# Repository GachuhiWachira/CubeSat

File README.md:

# CubeSat
Outer Casing Designs from Fusion 360

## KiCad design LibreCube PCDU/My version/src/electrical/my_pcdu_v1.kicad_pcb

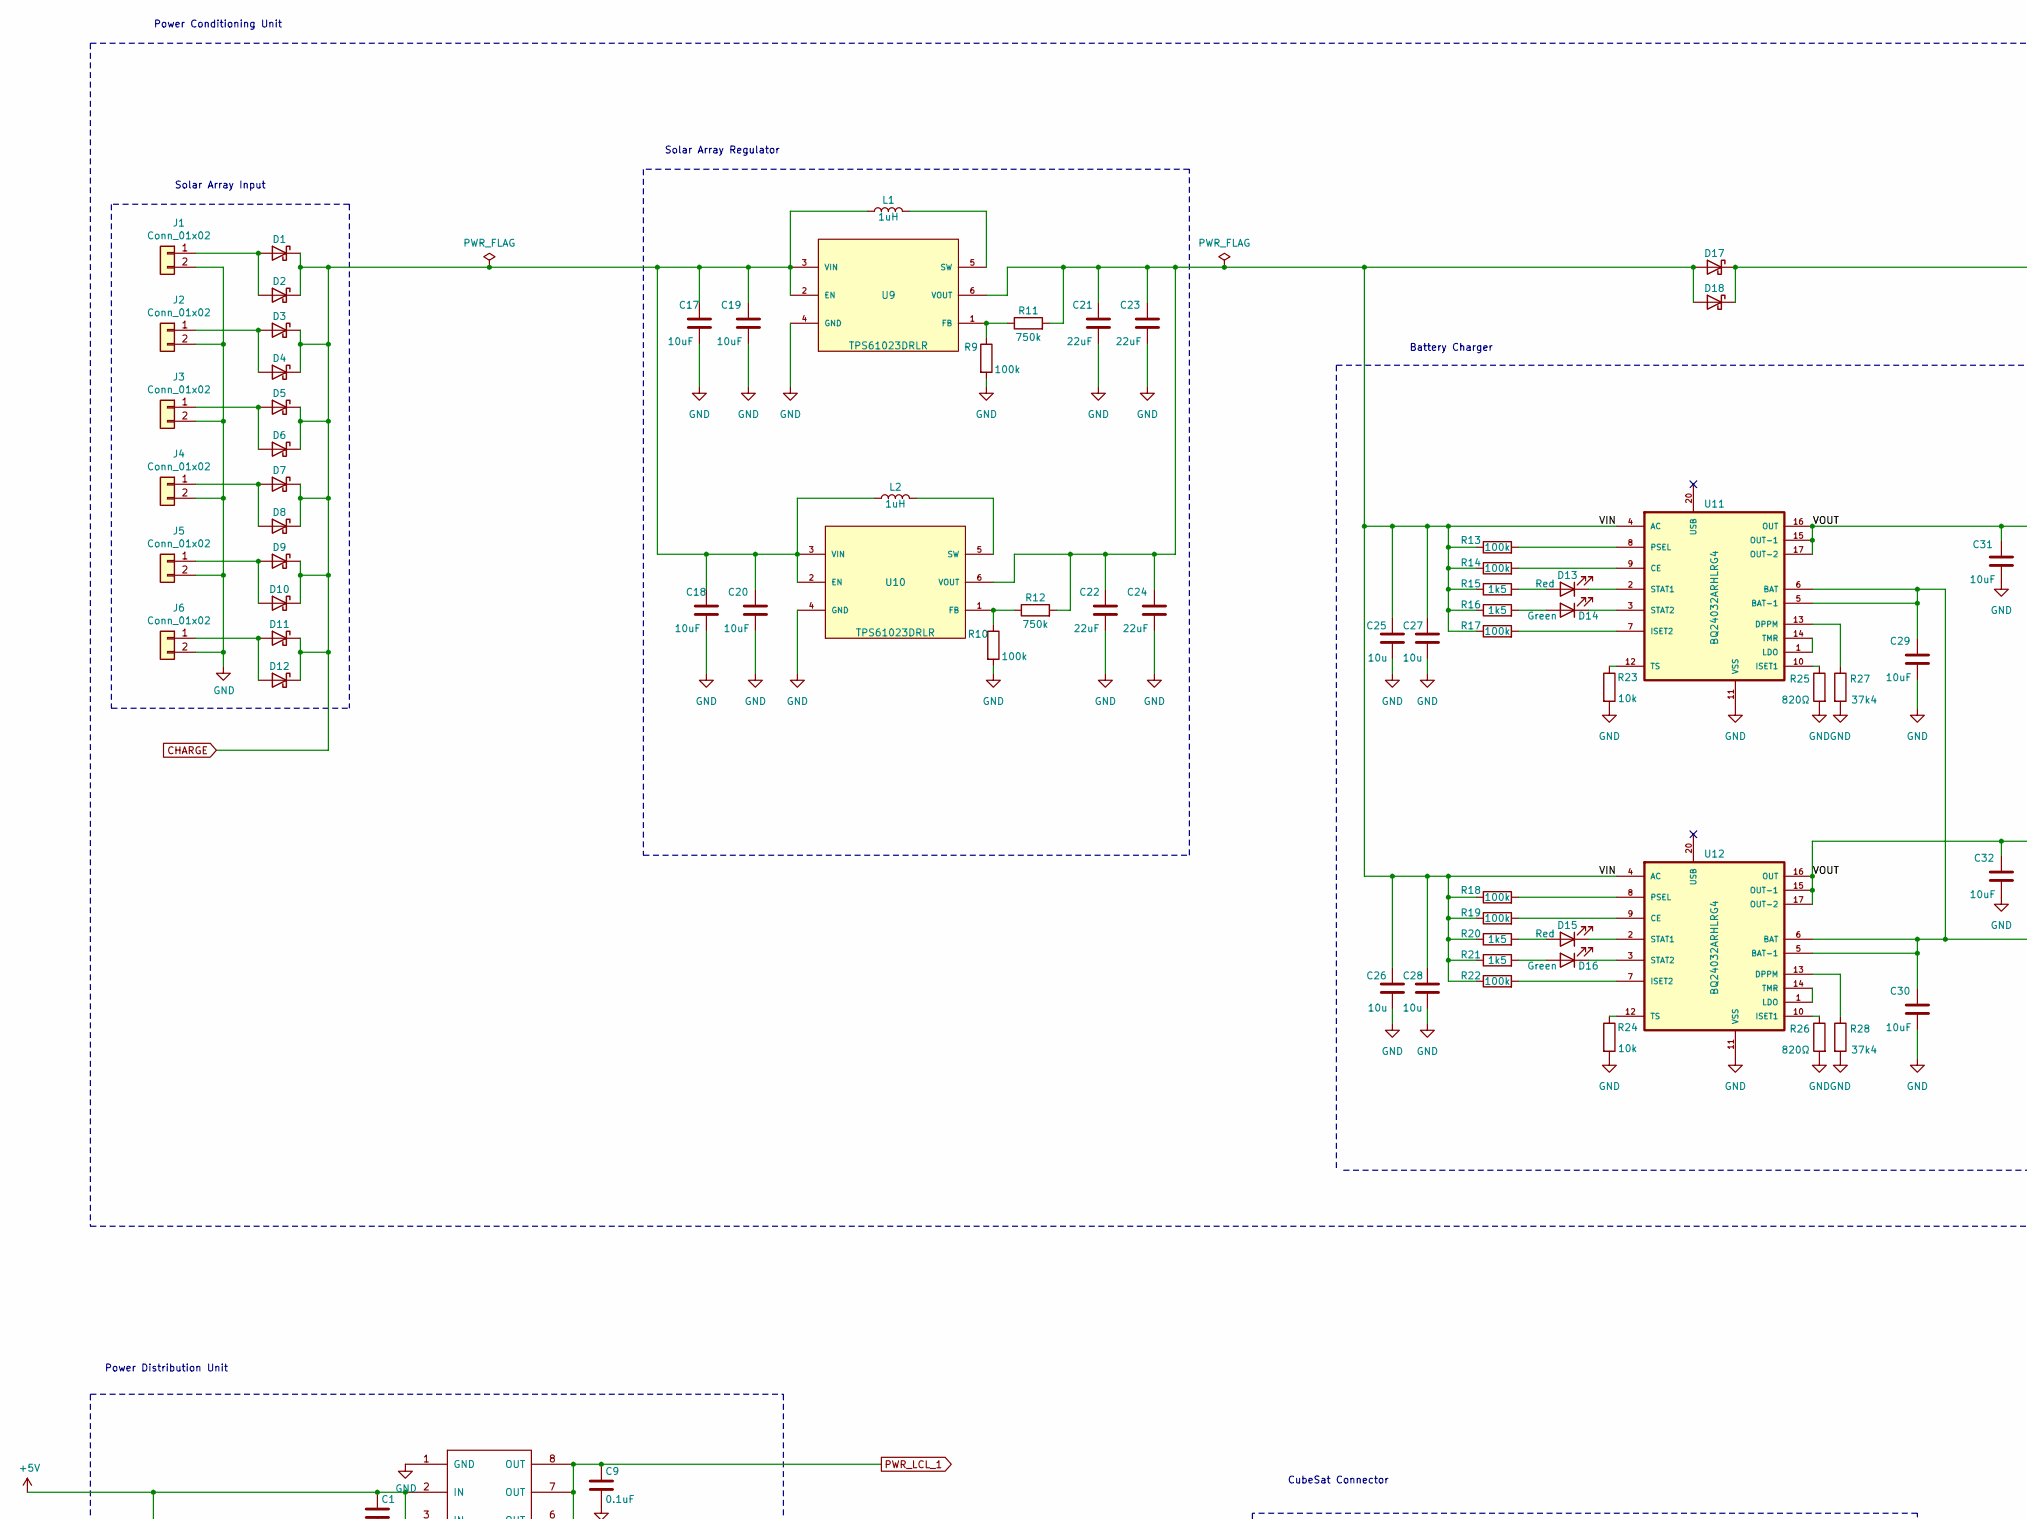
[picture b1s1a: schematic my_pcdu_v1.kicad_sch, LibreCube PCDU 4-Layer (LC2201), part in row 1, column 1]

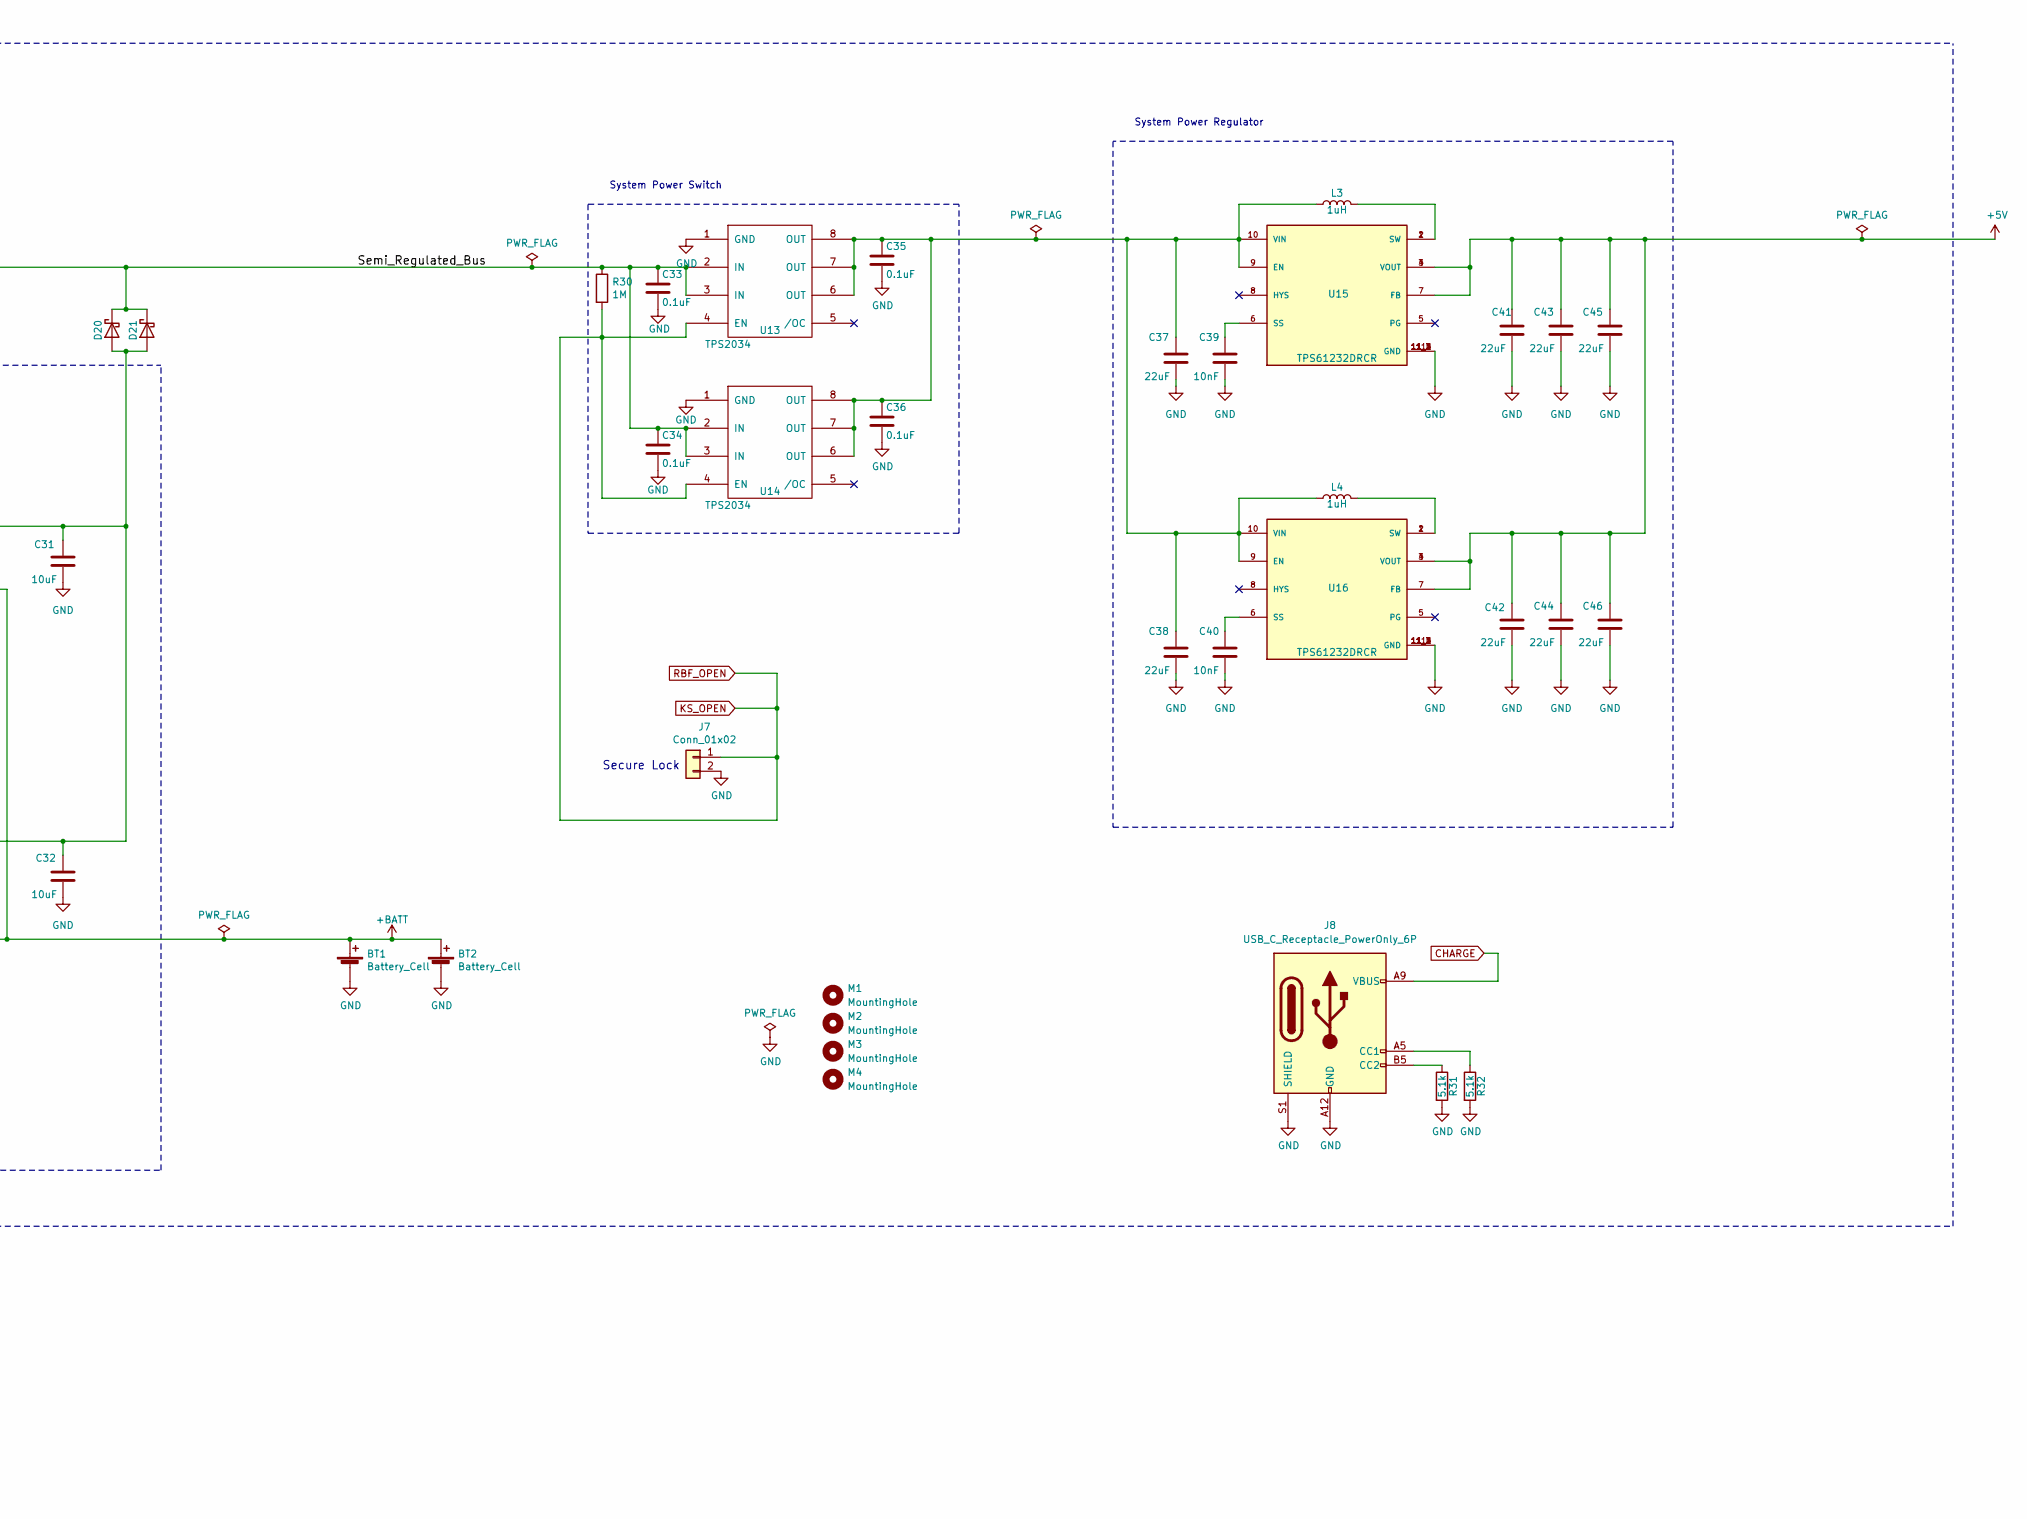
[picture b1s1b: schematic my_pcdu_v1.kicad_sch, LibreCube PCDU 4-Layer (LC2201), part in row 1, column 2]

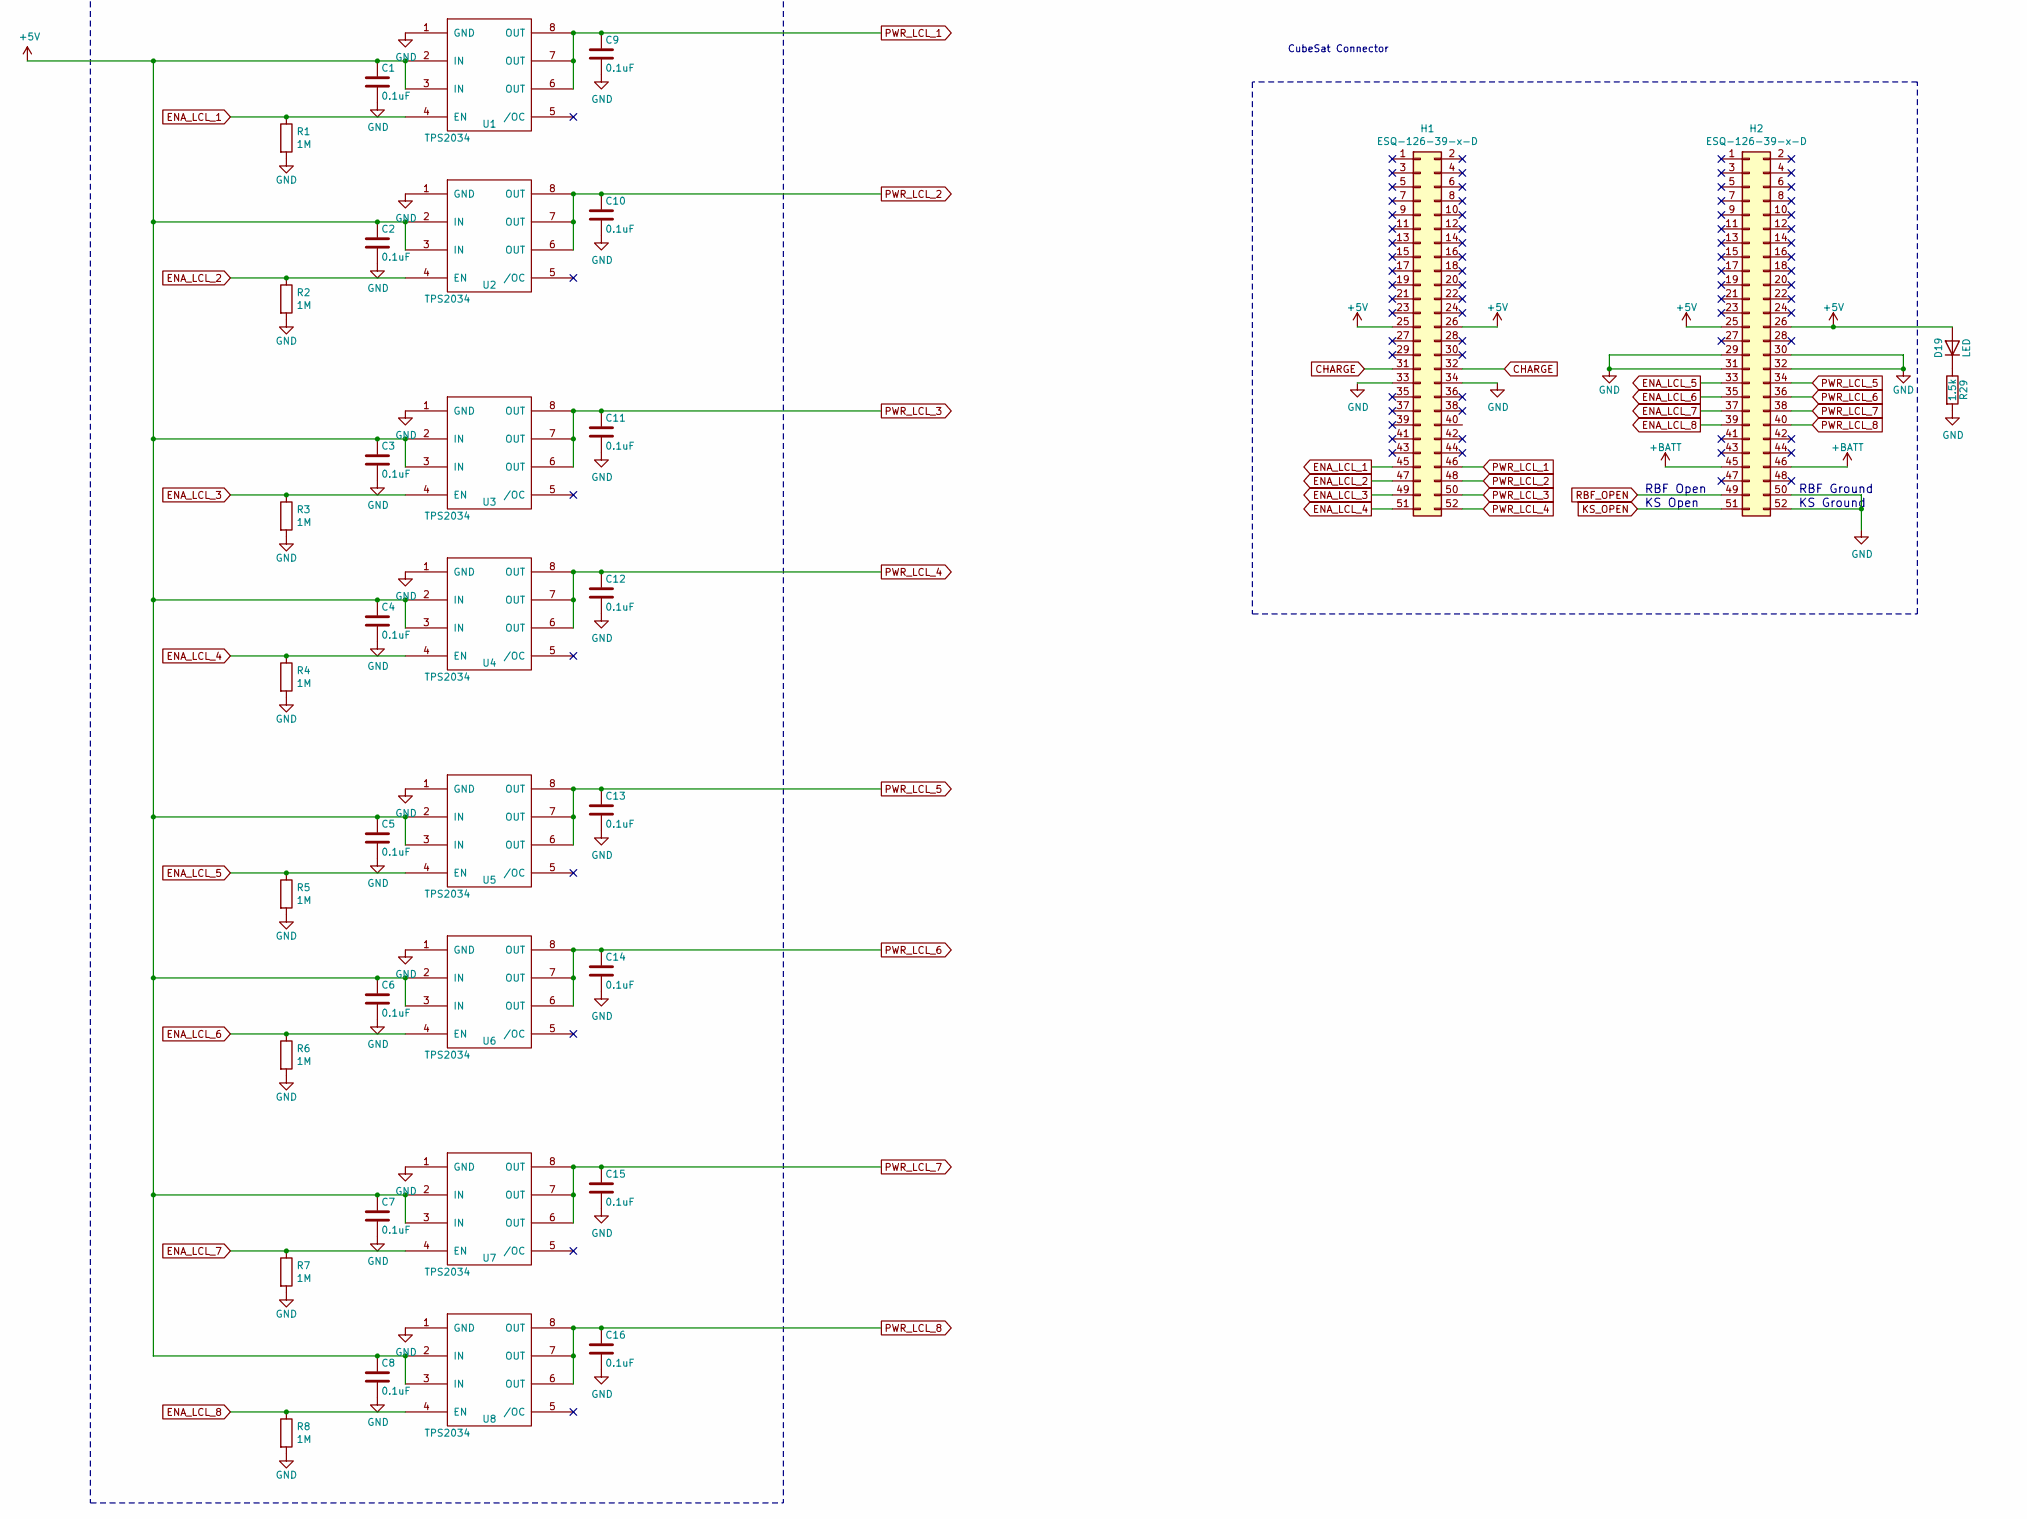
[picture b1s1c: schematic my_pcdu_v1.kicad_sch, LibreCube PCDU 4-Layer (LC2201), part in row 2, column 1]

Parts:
BT1, BT2: Battery_Cell; BatteryHolder_Keystone_1042_1x18650
C1, C2, C3, C4, C5, C6, C7, C8, C9, C10, C11, C12, C13, C14, C15, C16, C33, C34, C35, C36: 0.1uF; C_0805_2012Metric
C17, C18, C19, C20, C29, C30, C31, C32: 10uF; C_0805_2012Metric_Pad1.18x1.45mm_HandSolder
C21, C22, C23, C24, C37, C38, C41, C42, C43, C44, C45, C46: 22uF; C_0805_2012Metric_Pad1.18x1.45mm_HandSolder
C25, C26, C27, C28: 10u; C_1206_3216Metric_Pad1.33x1.80mm_HandSolder
C39, C40: 10nF; C_0805_2012Metric_Pad1.18x1.45mm_HandSolder
D1, D2, D3, D4, D5, D6, D7, D8, D9, D10, D11, D12, D17, D18, D20, D21: D_Schottky; D_SOD-123
D13, D15: Red; LED_0805_2012Metric_Pad1.15x1.40mm_HandSolder
D14, D16: Green; LED_0805_2012Metric_Pad1.15x1.40mm_HandSolder
D19: LED; D_0805_2012Metric
H1, H2: ESQ-126-39-x-D; PinHeader_2x26_P2.54mm_Vertical
J1, J2, J3, J4, J5, J6: Conn_01x02; PinHeader_1x02_P2.54mm_Horizontal
J7: Conn_01x02; PinHeader_1x02_P2.54mm_Vertical
J8: USB_C_Receptacle_PowerOnly_6P; USB_C_Receptacle_GCT_USB4125-xx-x-0190_6P_TopMnt_Horizontal
L1, L2, L3, L4: 1uH; L_Coilcraft_XAL4040-XXX
M1, M2, M3, M4: MountingHole; MountingHole_3.2mm_M3_Pad
R1, R2, R3, R4, R5, R6, R7, R8, R30: 1M; R_0805_2012Metric
R9, R10, R13, R14, R17, R18, R19, R22: 100k; R_0805_2012Metric_Pad1.20x1.40mm_HandSolder
R11, R12: 750k; R_0805_2012Metric_Pad1.20x1.40mm_HandSolder
R15, R16, R20, R21: 1k5; R_0805_2012Metric_Pad1.20x1.40mm_HandSolder
R23, R24: 10k; R_0805_2012Metric_Pad1.20x1.40mm_HandSolder
R25, R26: 820Ω; R_0805_2012Metric_Pad1.20x1.40mm_HandSolder
R27, R28: 37k4; R_0805_2012Metric_Pad1.20x1.40mm_HandSolder
R29: 1.5k; R_0805_2012Metric
R31, R32: 5.1k; R_0805_2012Metric
REF1: Logo_Open_Hardware_Small; OSHW-Logo_5.7x6mm_SilkScreen
U1, U2, U3, U4, U5, U6, U7, U8, U13, U14: TPS2034; SO-8_3.9x4.9mm_P1.27mm
U9, U10: TPS61023DRLR; DRL0006A; PARTNUMBER TPS61023DRL
U11, U12: BQ24032ARHLRG4; IC_MSP430FR2522IRHLR
U15, U16: TPS61232DRCR; VREG_TPS61232DRCR; PARTREV C

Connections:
+5V: C1.1, C2.1, C3.1, C4.1, C5.1, C6.1, C7.1, C8.1, C41.1, C42.1, C43.1, C44.1, C45.1, C46.1, D19.2 (A), H1.25, H1.26, H2.25, H2.26, U1.2 (IN), U1.3 (IN), U2.2 (IN), U2.3 (IN), U3.2 (IN), U3.3 (IN), U4.2 (IN), U4.3 (IN), U5.2 (IN), U5.3 (IN), U6.2 (IN), U6.3 (IN), U7.2 (IN), U7.3 (IN), U8.2 (IN), U8.3 (IN), U15.3 (VOUT), U15.4 (VOUT), U15.7 (FB), U16.3 (VOUT), U16.4 (VOUT), U16.7 (FB)
+BATT: BT1.1 (+), BT2.1 (+), C29.1, C30.1, H2.45, H2.46, U11.5 (BAT-1), U11.6 (BAT), U12.5 (BAT-1), U12.6 (BAT)
/Semi_Regulated_Bus: C33.1, C34.1, D17.1 (K), D18.1 (K), D20.1 (K), D21.1 (K), R30.1, U13.2 (IN), U13.3 (IN), U14.2 (IN), U14.3 (IN)
/VIN: C21.1, C22.1, C23.1, C24.1, C25.1, C26.1, C27.1, C28.1, D17.2 (A), D18.2 (A), R11.2, R12.2, R13.1, R14.1, R15.1, R16.1, R17.1, R18.1, R19.1, R20.1, R21.1, R22.1, U9.6 (VOUT), U10.6 (VOUT), U11.4 (AC), U12.4 (AC)
/VOUT: C31.1, C32.1, D20.2 (A), D21.2 (A), U11.15 (OUT-1), U11.16 (OUT), U11.17 (OUT-2), U12.15 (OUT-1), U12.16 (OUT), U12.17 (OUT-2)
CHARGE: C17.1, C18.1, C19.1, C20.1, D1.1 (K), D2.1 (K), D3.1 (K), D4.1 (K), D5.1 (K), D6.1 (K), D7.1 (K), D8.1 (K), D9.1 (K), D10.1 (K), D11.1 (K), D12.1 (K), H1.31, H1.32, J8.A9 (VBUS), J8.B9 (VBUS), L1.1, L2.1, U9.2 (EN), U9.3 (VIN), U10.2 (EN), U10.3 (VIN)
ENA_LCL_1: H1.45, R1.1, U1.4 (EN)
ENA_LCL_2: H1.47, R2.1, U2.4 (EN)
ENA_LCL_3: H1.49, R3.1, U3.4 (EN)
ENA_LCL_4: H1.51, R4.1, U4.4 (EN)
ENA_LCL_5: H2.33, R5.1, U5.4 (EN)
ENA_LCL_6: H2.35, R6.1, U6.4 (EN)
ENA_LCL_7: H2.37, R7.1, U7.4 (EN)
ENA_LCL_8: H2.39, R8.1, U8.4 (EN)
GND: BT1.2 (-), BT2.2 (-), C1.2, C2.2, C3.2, C4.2, C5.2, C6.2, C7.2, C8.2, C9.2, C10.2, C11.2, C12.2, C13.2, C14.2, C15.2, C16.2, C17.2, C18.2, C19.2, C20.2, C21.2, C22.2, C23.2, C24.2, C25.2, C26.2, C27.2, C28.2, C29.2, C30.2, C31.2, C32.2, C33.2, C34.2, C35.2, C36.2, C37.2, C38.2, C39.2, C40.2, C41.2, C42.2, C43.2, C44.2, C45.2, C46.2, H1.33, H1.34, H2.29, H2.30, H2.31, H2.32, H2.50, H2.52, J1.2, J2.2, J3.2, J4.2, J5.2, J6.2, J7.2, J8.A12 (GND), J8.B12 (GND), J8.S1 (SHIELD), R1.2, R2.2, R3.2, R4.2, R5.2, R6.2, R7.2, R8.2, R9.2, R10.2, R23.2, R24.2, R25.2, R26.2, R27.2, R28.2, R29.2, R31.2, R32.2, U1.1 (GND), U2.1 (GND), U3.1 (GND), U4.1 (GND), U5.1 (GND), U6.1 (GND), U7.1 (GND), U8.1 (GND), U9.4 (GND), U10.4 (GND), U11.11 (VSS), U11.21 (PwrPad), U11.22, U11.23, U11.24, U11.25, U11.26, U11.27, U11.28, U11.29, U12.11 (VSS), U12.21 (PwrPad), U12.22, U12.23, U12.24, U12.25, U12.26, U12.27, U12.28, U12.29, U13.1 (GND), U14.1 (GND), U15.11 (GND), U15.11_1 (GND), U15.11_2 (GND), U15.11_3 (GND), U15.11_4 (GND), U16.11 (GND), U16.11_1 (GND), U16.11_2 (GND), U16.11_3 (GND), U16.11_4 (GND)
KS_OPEN: H2.49, H2.51, J7.1, R30.2, U13.4 (EN), U14.4 (EN)
unnamed: D1.2 (A), D2.2 (A), J1.1
unnamed: D3.2 (A), D4.2 (A), J2.1
unnamed: D5.2 (A), D6.2 (A), J3.1
unnamed: D7.2 (A), D8.2 (A), J4.1
unnamed: D9.2 (A), D10.2 (A), J5.1
unnamed: D11.2 (A), D12.2 (A), J6.1
unnamed: D13.2 (A), R15.2
unnamed: D13.1 (K), U11.2 (STAT1)
unnamed: D14.2 (A), R16.2
unnamed: D14.1 (K), U11.3 (STAT2)
unnamed: D15.2 (A), R20.2
unnamed: D15.1 (K), U12.2 (STAT1)
unnamed: D16.2 (A), R21.2
unnamed: D16.1 (K), U12.3 (STAT2)
unnamed: D19.1 (K), R29.1
unnamed: J8.A5 (CC1), R32.1
unnamed: J8.B5 (CC2), R31.1
unnamed: L3.2, U15.1 (SW), U15.2 (SW)
unnamed: L4.2, U16.1 (SW), U16.2 (SW)
unnamed: R9.1, R11.1, U9.1 (FB)
unnamed: L1.2, U9.5 (SW)
unnamed: R10.1, R12.1, U10.1 (FB)
unnamed: L2.2, U10.5 (SW)
unnamed: R14.2, U11.9 (CE)
unnamed: R27.1, U11.13 (DPPM)
unnamed: R25.1, U11.10 (ISET1)
unnamed: R17.2, U11.7 (ISET2)
unnamed: U11.1 (LDO), U11.14 (TMR)
unnamed: R13.2, U11.8 (PSEL)
unnamed: R23.1, U11.12 (TS)
unnamed: R19.2, U12.9 (CE)
unnamed: R28.1, U12.13 (DPPM)
unnamed: R26.1, U12.10 (ISET1)
unnamed: R22.2, U12.7 (ISET2)
unnamed: U12.1 (LDO), U12.14 (TMR)
unnamed: R18.2, U12.8 (PSEL)
unnamed: R24.1, U12.12 (TS)
unnamed: C35.1, C36.1, C37.1, C38.1, L3.1, L4.1, U13.6 (OUT), U13.7 (OUT), U13.8 (OUT), U14.6 (OUT), U14.7 (OUT), U14.8 (OUT), U15.9 (EN), U15.10 (VIN), U16.9 (EN), U16.10 (VIN)
unnamed: C39.1, U15.6 (SS)
unnamed: C40.1, U16.6 (SS)
PWR_LCL_1: C9.1, H1.46, U1.6 (OUT), U1.7 (OUT), U1.8 (OUT)
PWR_LCL_2: C10.1, H1.48, U2.6 (OUT), U2.7 (OUT), U2.8 (OUT)
PWR_LCL_3: C11.1, H1.50, U3.6 (OUT), U3.7 (OUT), U3.8 (OUT)
PWR_LCL_4: C12.1, H1.52, U4.6 (OUT), U4.7 (OUT), U4.8 (OUT)
PWR_LCL_5: C13.1, H2.34, U5.6 (OUT), U5.7 (OUT), U5.8 (OUT)
PWR_LCL_6: C14.1, H2.36, U6.6 (OUT), U6.7 (OUT), U6.8 (OUT)
PWR_LCL_7: C15.1, H2.38, U7.6 (OUT), U7.7 (OUT), U7.8 (OUT)
PWR_LCL_8: C16.1, H2.40, U8.6 (OUT), U8.7 (OUT), U8.8 (OUT)

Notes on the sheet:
KS Open
Solar Array Input
Solar Array Regulator
Power Distribution Unit
Secure Lock
System Power Switch
KS Ground
RBF Open
System Power Regulator
Battery Charger
CubeSat Connector
Power Conditioning Unit
RBF Ground

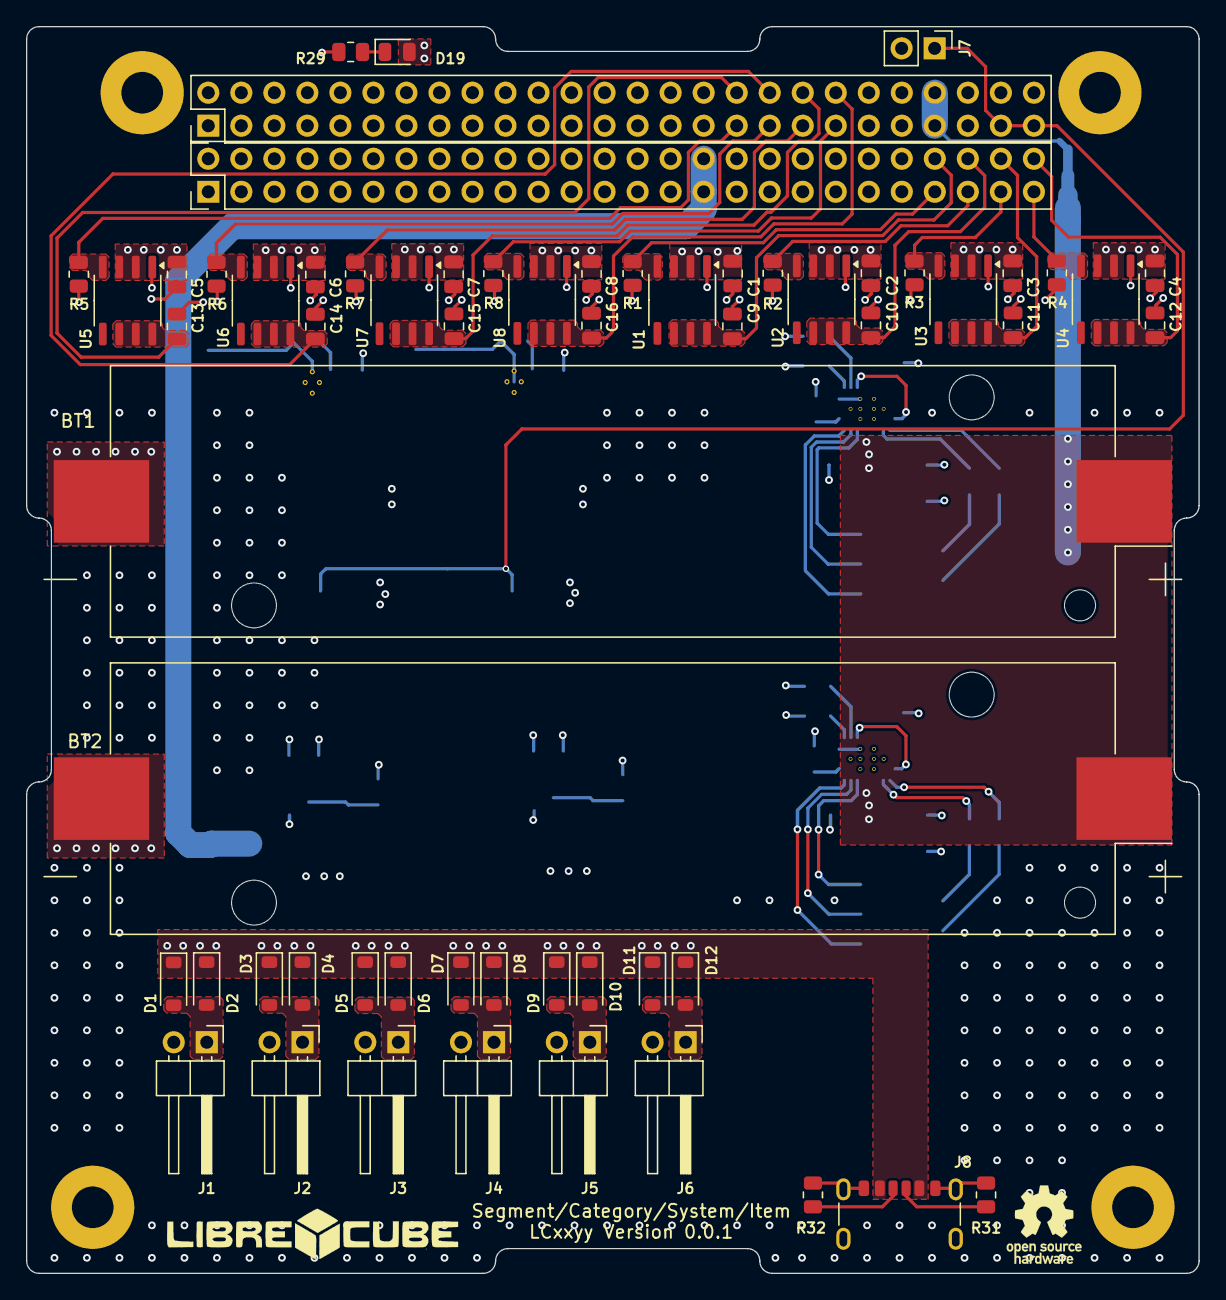
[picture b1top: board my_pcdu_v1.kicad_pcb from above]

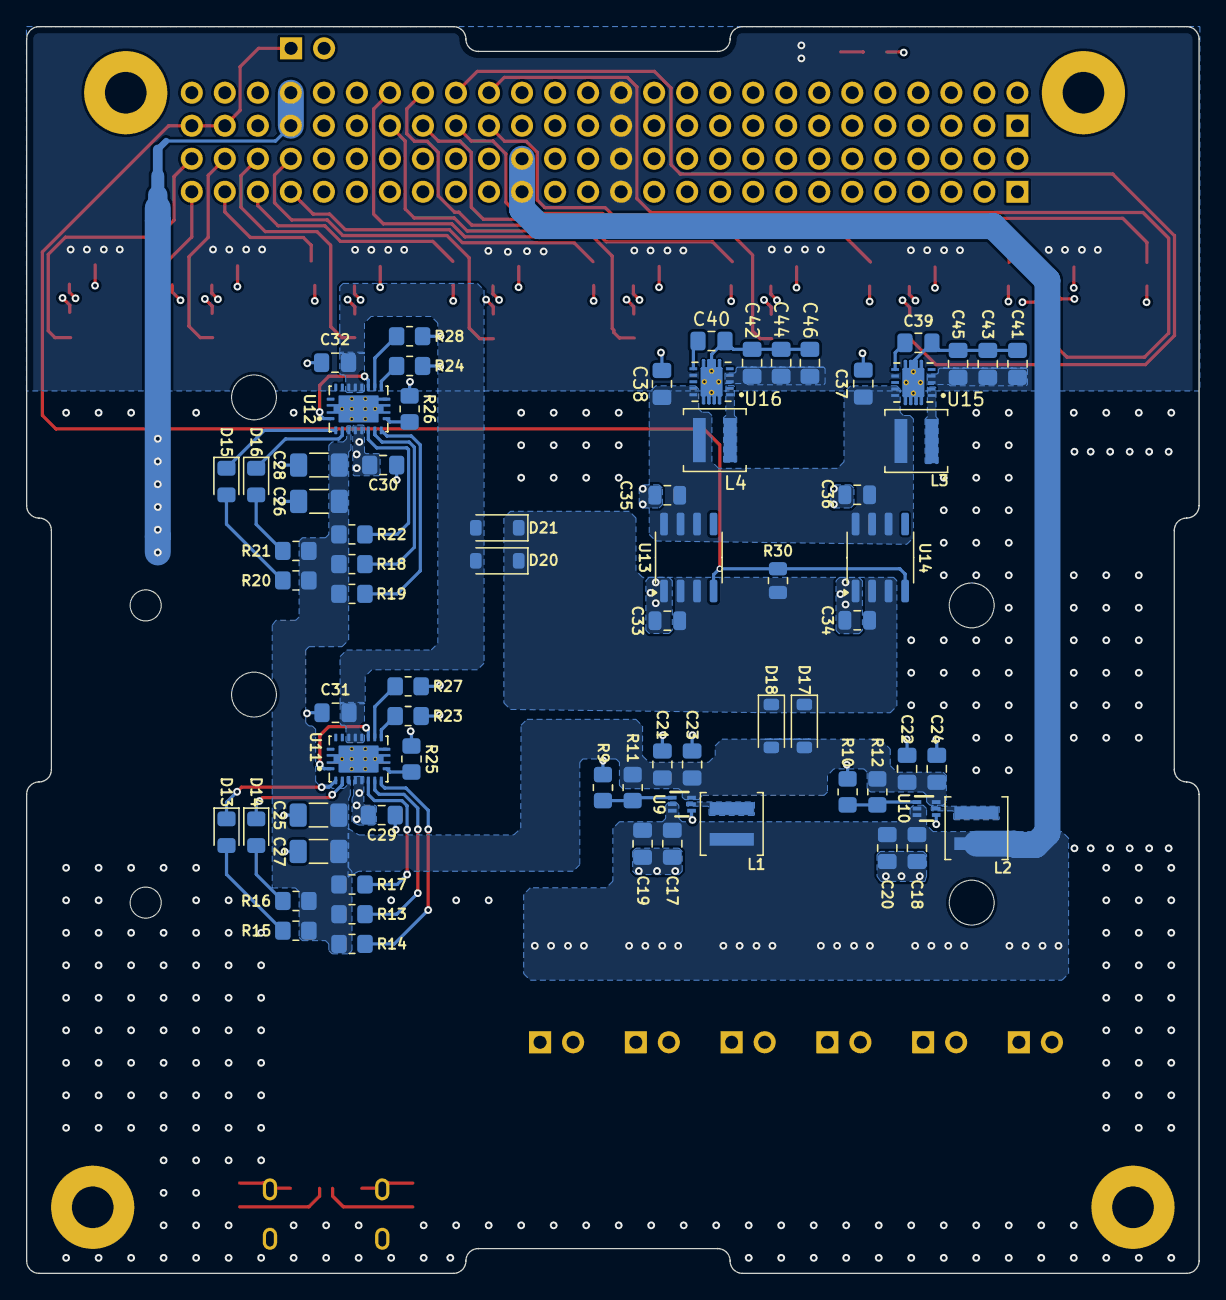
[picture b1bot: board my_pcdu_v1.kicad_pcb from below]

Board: 4 copper layers, 90.2 x 95.9 mm, 136 parts (71 on the bottom side), 64 nets.
